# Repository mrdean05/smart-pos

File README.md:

<h2> Battery Powered Two-Layer PCB <h2>

__Note - This is an ongoing project__

## Introduction
This project describes the design and development of a battery-powered, two-layer PCB for a smart point-of-sale (POS) device. The smart point-of-sale device is intended to work with a barcode scanner, identifying items and products with barcode IDs. It comes with a TFT screen and a GUI displaying the product details, including the brand, type, weight, and cost.

## Background of Project
There are numerous small to medium enterprises in Ghana that lack an effective way to track their inventory and finances. The existing implementations are very bulky and expensive, with software that is difficult for an average small shop owner to navigate, and with outrageous monthly subscriptions. This smart point-of-sale (POS) device seeks to simplify and improve the existing solution by creating a quick-to-use, cheap, and portable device. It works with a mobile application that updates the shop owner on every item bought in the shop, giving the shop owner visibility over their shop without their physical presence.

## Hardware and Circuit Design
The PCB was design and developed using KiCad. It comprises of multiple ICs (micocontroller, convertor ICs, and others).

* The Micrcontroller used is the ESP32s3. ESP32s3 is a System-On-Chip(SoC) integrating WiFi and Bluetooth, with peripherals that enable connection with other ICs and modules. 

* The PCBs also integrates ICs such
    - **SY8089 Buck Power Converter** that reduces the input voltage from 5V to 3.3V for the microcontroller and other components in the circuit. It has about 2A output current, with capacitors used as noise filters.
    - **TP4056 and DW01A** that ensure battery health safety by preventing under and over charging.
    - **MAX17048** as a current fuel gauge for the battery.
    - **PCF8523T** serves as an RTC module providing precise time and date information. It is supplied by a coin battery that ensures its continual performance when the device is off.
    - **TCA8418** serves as a keypad scan device through which users can interact with the POS device.
    - **W25N02KVZEIR and W25Q256JVEIQ** that serves as additional flash memory.
    - **PCA95548** serves as additional gpios.

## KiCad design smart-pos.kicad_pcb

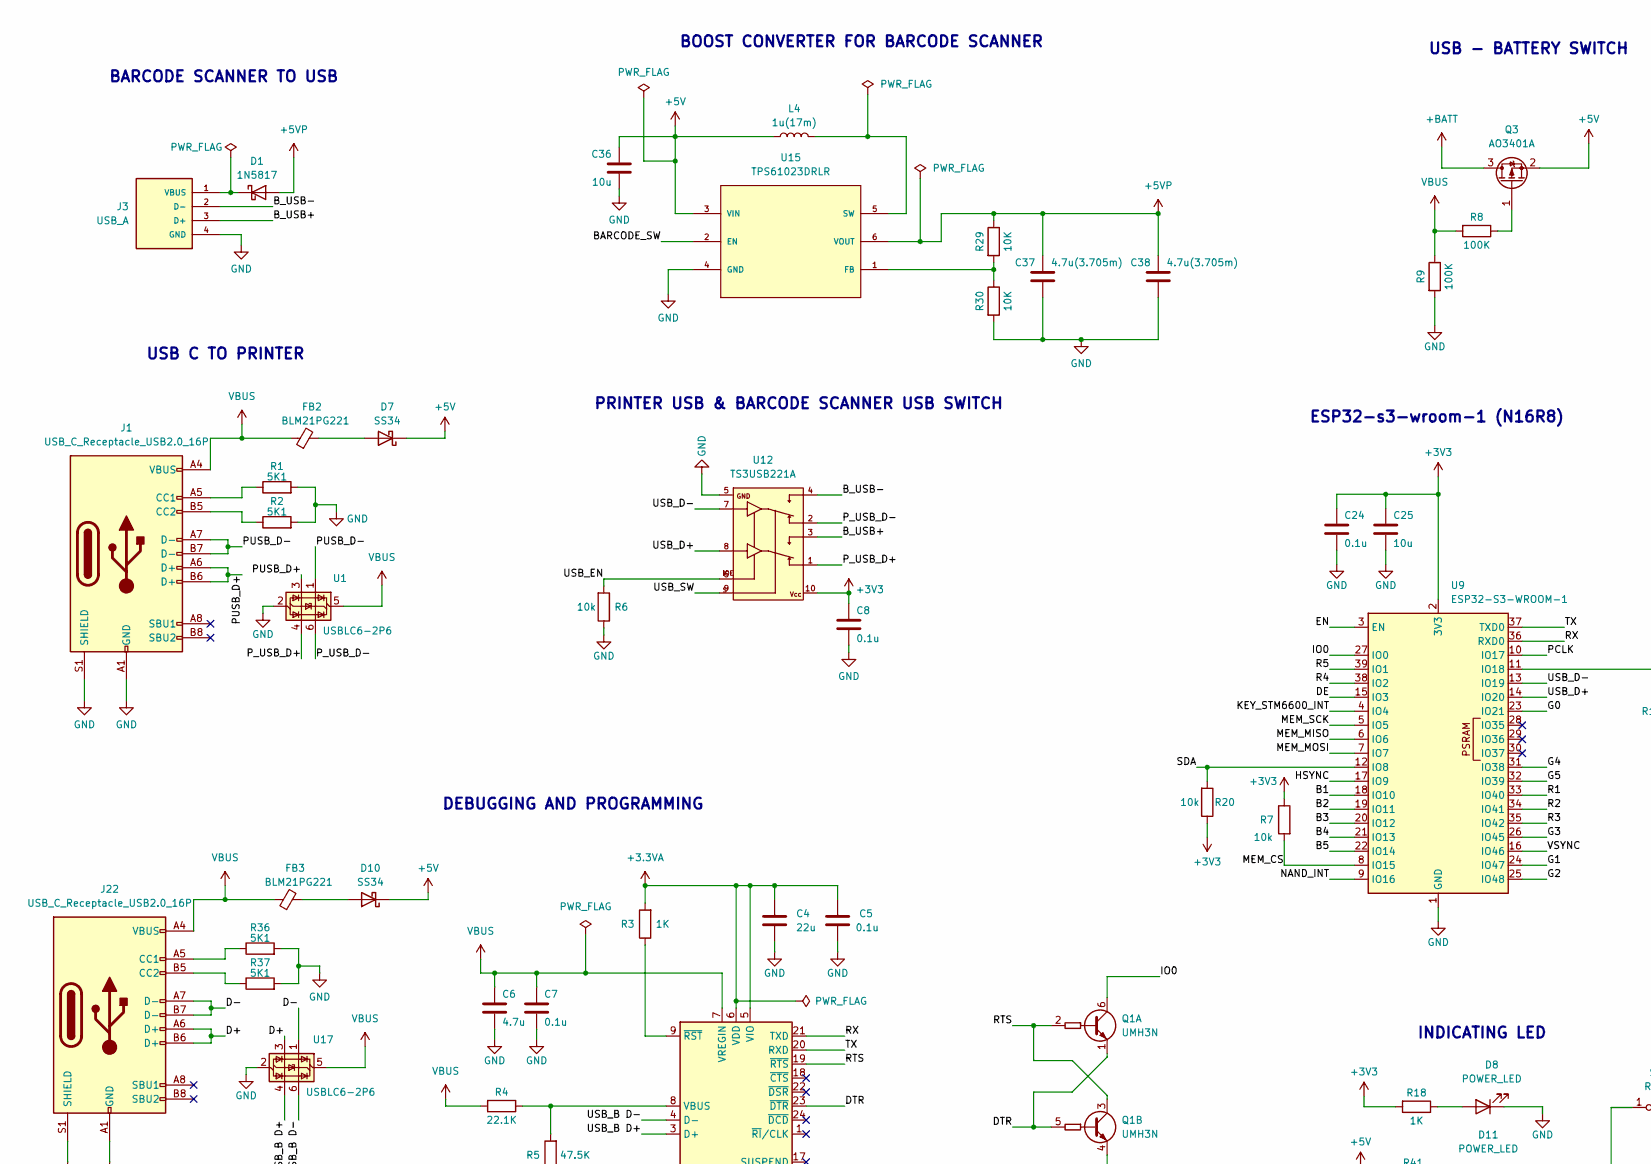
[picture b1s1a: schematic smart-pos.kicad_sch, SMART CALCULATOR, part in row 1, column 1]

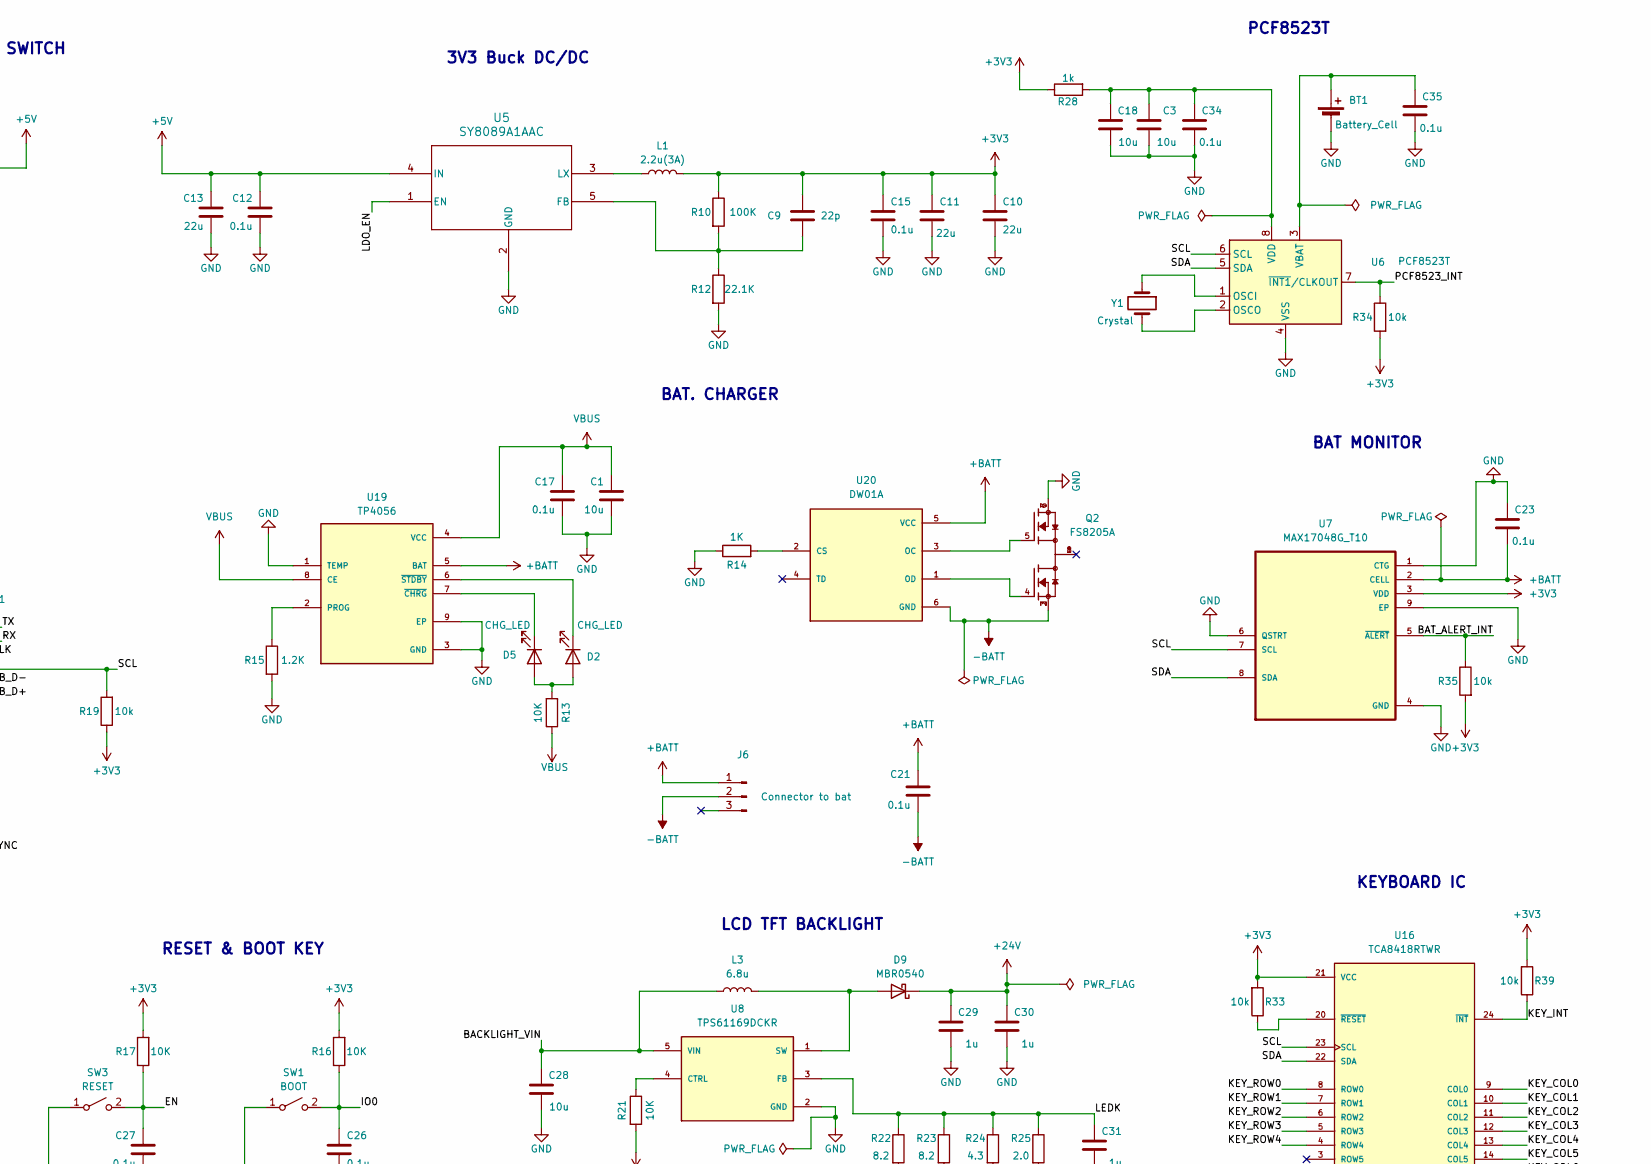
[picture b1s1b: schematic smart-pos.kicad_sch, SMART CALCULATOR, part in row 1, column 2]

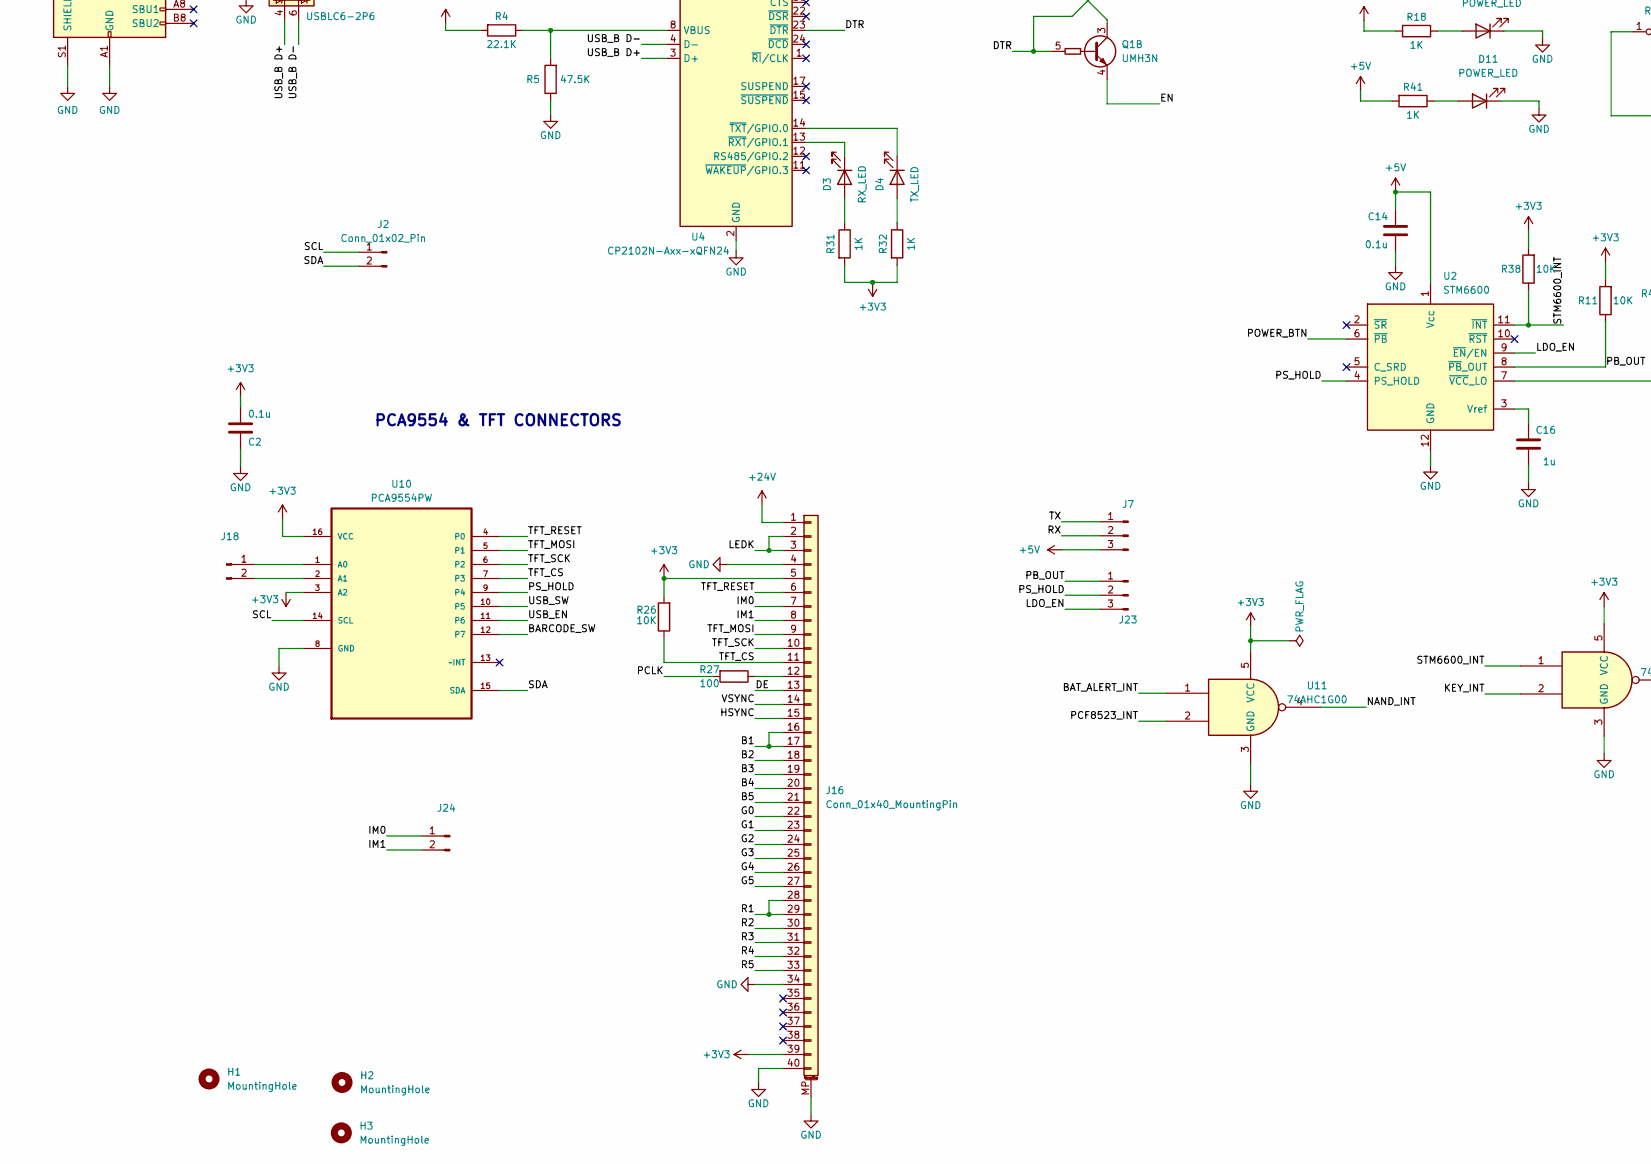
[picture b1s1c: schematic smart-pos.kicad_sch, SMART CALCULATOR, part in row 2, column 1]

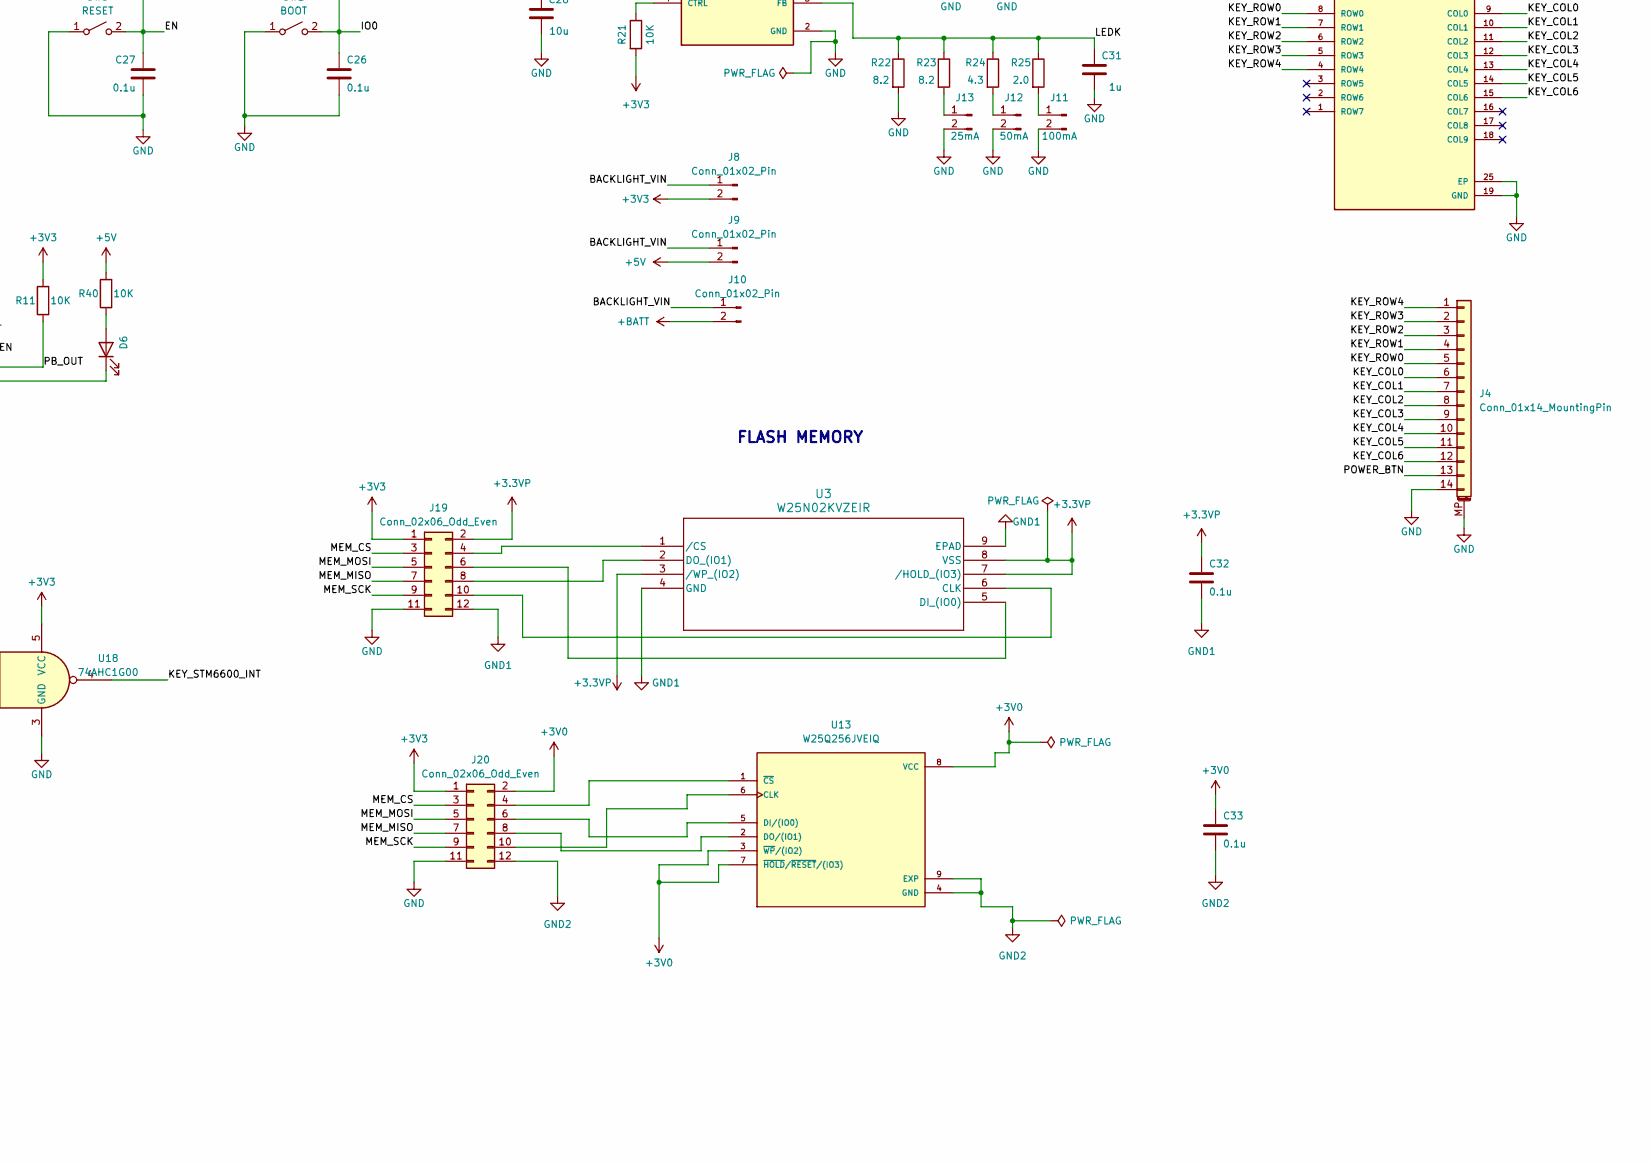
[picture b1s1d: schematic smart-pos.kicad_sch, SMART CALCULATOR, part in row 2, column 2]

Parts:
BT1: Battery_Cell; Battery_Panasonic_CR2032-HFN_Horizontal_CircularHoles
C1, C3, C18, C25, C28, C36: 10u; C_0603_1608Metric_Pad1.08x0.95mm_HandSolder
C2, C5, C7, C8, C12, C14, C15, C17, C21, C23, C24, C26, C27, C32, C33, C34, C35: 0.1u; C_0603_1608Metric_Pad1.08x0.95mm_HandSolder
C4, C10, C11, C13: 22u; C_0603_1608Metric_Pad1.08x0.95mm_HandSolder
C6: 4.7u; C_0603_1608Metric_Pad1.08x0.95mm_HandSolder
C9: 22p; C_0603_1608Metric_Pad1.08x0.95mm_HandSolder
C16, C29, C30, C31: 1u; C_0603_1608Metric_Pad1.08x0.95mm_HandSolder
C37, C38: 4.7u(3.705m); C_0603_1608Metric_Pad1.08x0.95mm_HandSolder
D1: 1N5817; D_SOD-123
D2, D5: CHG_LED; LED_0603_1608Metric_Pad1.05x0.95mm_HandSolder
D3, D6: RX_LED; LED_0603_1608Metric_Pad1.05x0.95mm_HandSolder
D4: TX_LED; LED_0603_1608Metric_Pad1.05x0.95mm_HandSolder
D7, D10: SS34; D_SMA_Handsoldering
D8, D11: POWER_LED; LED_0603_1608Metric_Pad1.05x0.95mm_HandSolder
D9: MBR0540; D_SOD-123
FB2, FB3: BLM21PG221; L_0805_2012Metric_Pad1.05x1.20mm_HandSolder
H1, H2, H3: MountingHole; MountingHole_2.1mm
J1, J22: USB_C_Receptacle_USB2.0_16P; USB_C_Receptacle_GCT_USB4105-xx-A_16P_TopMnt_Horizontal
J2, J8, J9, J10, J18, J24: Conn_01x02_Pin; PinHeader_1x02_P2.54mm_Vertical
J3: USB_A; OST_USB-A1HSW6; PARTREV A
J4: Conn_01x14_MountingPin; Hirose_FH12-14S-0.5SH_1x14-1MP_P0.50mm_Horizontal
J6: Connector to bat; JST_PH_S3B-PH-K_1x03_P2.00mm_Horizontal
J7, J23: Connector to IM0; PinHeader_1x03_P2.54mm_Vertical
J11: 100mA; PinHeader_1x02_P2.54mm_Vertical
J12: 50mA; PinHeader_1x02_P2.54mm_Vertical
J13: 25mA; PinHeader_1x02_P2.54mm_Vertical
J16: Conn_01x40_MountingPin; Hirose_FH12-40S-0.5SH_1x40-1MP_P0.50mm_Horizontal
J19, J20: Conn_02x06_Odd_Even; PinHeader_2x06_P2.54mm_Vertical
L1: 2.2u(3A); L_Cenker_CKCS6045
L3: 6.8u; L_Cenker_CKCS6020
L4: 1u(17m); L_Cenker_CKCS4018
Q1: UMH3N; SOT-363_SC-70-6
Q2: FS8205A; SOT-23-6_Handsoldering; PARTREV 1.7
Q3: AO3401A; SOT-23
R1, R2, R36, R37: 5K1; R_0603_1608Metric_Pad0.98x0.95mm_HandSolder
R3, R14, R18, R31, R32, R41: 1K; R_0603_1608Metric_Pad0.98x0.95mm_HandSolder
R4, R12: 22.1K; R_0603_1608Metric_Pad0.98x0.95mm_HandSolder
R5: 47.5K; R_0603_1608Metric_Pad0.98x0.95mm_HandSolder
R6, R7, R19, R20, R33, R34, R35, R39: 10k; R_0603_1608Metric_Pad0.98x0.95mm_HandSolder
R8, R9, R10: 100K; R_0603_1608Metric_Pad0.98x0.95mm_HandSolder
R11, R13, R16, R17, R21, R26, R29, R30, R38, R40: 10K; R_0603_1608Metric_Pad0.98x0.95mm_HandSolder
R15: 1.2K; R_0603_1608Metric_Pad0.98x0.95mm_HandSolder
R22, R23: 8.2; R_0603_1608Metric_Pad0.98x0.95mm_HandSolder
R24: 4.3; R_0603_1608Metric_Pad0.98x0.95mm_HandSolder
R25: 2.0; R_0603_1608Metric_Pad0.98x0.95mm_HandSolder
R27: 100; R_0603_1608Metric_Pad0.98x0.95mm_HandSolder
R28: 1k; R_0603_1608Metric_Pad0.98x0.95mm_HandSolder
SW1: BOOT; SW_SPST_PTS810
SW3: RESET; SW_SPST_PTS810
U1, U17: USBLC6-2P6; SOT-666
U2: STM6600; TDFN-12_2x3mm_P0.5mm
U3: W25N02KVZEIR; W25N02-M
U4: CP2102N-Axx-xQFN24; QFN-24-1EP_4x4mm_P0.5mm_EP2.6x2.6mm
U5: SY8089A1AAC; SY8089AAAC_SGY
U6: PCF8523T; SOIC-8_3.9x4.9mm_P1.27mm
U7: MAX17048G_T10; SON50P200X200X80-9N
U8: TPS61169DCKR; SOT65P210X110-5N; PARTREV A
U9: ESP32-S3-WROOM-1
U10: PCA9554PW; SOP65P640X120-16N; MPN PCA9554PW
U11, U18: 74AHC1G00; SOT-23-5_HandSoldering
U12: TS3USB221A; QFN-10-RSE
U13: W25Q256JVEIQ; SON127P600X800X80-9N; PARTREV G
U15: TPS61023DRLR; DRL0006A; PARTNUMBER TPS61023DRL
U16: TCA8418RTWR; QFN50P400X400X80-25N; PARTREV G
U19: TP4056; SOP127P600X175-9N
U20: DW01A; SOT-23-6_Handsoldering; PARTREV 1.8
Y1: Crystal; Crystal_C26-LF_D2.1mm_L6.5mm_Horizontal

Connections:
+3.3VA: C4.1, C5.1, R3.2, U4.5 (VIO), U4.6 (VDD)
+3.3VP: C32.1, J19.2, U3.3 (/WP_(IO2)), U3.7 (/HOLD_(IO3)), U3.8 (VSS)
+3V0: C33.1, J20.2, U13.3 (~WP/(IO2)), U13.7 (~HOLD/~RESET/(IO3)), U13.8 (VCC)
+3V3: C2.2, C8.1, C9.1, C10.1, C11.1, C15.1, C24.1, C25.1, J8.2, J16.5, J16.39, J19.1, J20.1, L1.2, R7.1, R10.1, R11.2, R16.2, R17.2, R18.2, R19.1, R20.1, R21.2, R26.2, R28.1, R31.2, R32.2, R33.2, R34.2, R35.2, R38.2, R39.2, U7.3 (VDD), U9.2 (3V3), U10.3 (A2), U10.16 (VCC), U11.5 (VCC), U12.10, U16.21 (VCC), U18.5 (VCC)
+5V: C12.1, C13.1, C14.1, C36.1, D7.1 (K), D10.1 (K), J7.3, J9.2, L4.1, Q3.2 (S), R40.2, R41.2, U2.1 (Vcc), U5.4 (IN), U15.3 (VIN); also elsewhere on the board
+5VP: C37.1, C38.1, D1.2 (A), R29.1, U15.6 (VOUT)
+24V: C29.1, C30.1, D9.1 (K), J16.1
+BATT: C21.1, C23.2, J6.1, J10.2, Q3.3 (D), U7.2 (CELL), U19.5 (BAT), U20.5 (VCC)
-BATT: C21.2, J6.2, Q2.2, Q2.3, U20.6 (GND)
/B1: J16.16, J16.17, U9.18 (IO10)
/B2: J16.18, U9.19 (IO11)
/B3: J16.19, U9.20 (IO12)
/B4: J16.20, U9.21 (IO13)
/B5: J16.21, U9.22 (IO14)
/BACKLIGHT_VIN: C28.1, J8.1, J9.1, J10.1, L3.1, U8.5 (VIN)
/BARCODE_SW: U10.12 (P7), U15.2 (EN)
/BAT_ALERT_INT: R35.1, U7.5 (~ALERT), U11.1
/B_USB+: J3.3 (D+), U12.3
/B_USB-: J3.2 (D-), U12.4
/D+: J22.A6 (D+), J22.B6 (D+), U17.3 (I/O2)
/D-: J22.A7 (D-), J22.B7 (D-), U17.1 (I/O1)
/DE: J16.13, U9.15 (IO3)
/DTR: Q1.1 (E1), Q1.5 (B2), U4.23 (~DTR)
/EN: C27.1, Q1.4 (E2), R17.1, SW3.2 (B), U9.3 (EN)
/G0: J16.22, U9.23 (IO21)
/G1: J16.23, U9.24 (IO47)
/G2: J16.24, U9.25 (IO48)
/G3: J16.25, U9.26 (IO45)
/G4: J16.26, U9.31 (IO38)
/G5: J16.27, U9.32 (IO39)
/HSYNC: J16.15, U9.17 (IO9)
/IM0: J16.7, J24.1
/IM1: J16.8, J24.2
/IO0: C26.1, Q1.6 (C1), R16.1, SW1.2 (B), U9.27 (IO0)
/KEY_COL0: J4.6, U16.9 (COL0)
/KEY_COL1: J4.7, U16.10 (COL1)
/KEY_COL2: J4.8, U16.11 (COL2)
/KEY_COL3: J4.9, U16.12 (COL3)
/KEY_COL4: J4.10, U16.13 (COL4)
/KEY_COL5: J4.11, U16.14 (COL5)
/KEY_COL6: J4.12, U16.15 (COL6)
/KEY_INT: R39.1, U16.24 (~INT), U18.2
/KEY_ROW0: J4.5, U16.8 (ROW0)
/KEY_ROW1: J4.4, U16.7 (ROW1)
/KEY_ROW2: J4.3, U16.6 (ROW2)
/KEY_ROW3: J4.2, U16.5 (ROW3)
/KEY_ROW4: J4.1, U16.4 (ROW4)
/KEY_STM6600_INT: U9.4 (IO4), U18.4
/LDO_EN: J23.3, U2.9 (~EN/EN), U5.1 (EN)
/LEDK: C31.1, J16.2, J16.3, R22.1, R23.1, R24.1, R25.1, U8.3 (FB)
/MEM_CS: J19.3, J20.3, R7.2, U9.8 (IO15)
/MEM_MISO: J19.7, J20.7, U9.6 (IO6)
/MEM_MOSI: J19.5, J20.5, U9.7 (IO7)
/MEM_SCK: J19.9, J20.9, U9.5 (IO5)
/NAND_INT: U9.9 (IO16), U11.4
/PB_OUT: J23.1, R11.1, U2.8 (~PB_OUT)
/PCF8523_INT: R34.1, U6.7 (~INT1/CLKOUT), U11.2
/PCLK: R27.2, U9.10 (IO17)
/POWER_BTN: J4.13, U2.6 (~PB)
/PS_HOLD: J23.2, U2.4 (PS_HOLD), U10.9 (P4)
/PUSB_D+: J1.A6 (D+), J1.B6 (D+), U1.3 (I/O2)
/PUSB_D-: J1.A7 (D-), J1.B7 (D-), U1.1 (I/O1)
/P_USB_D+: U1.4 (I/O2), U12.1
/P_USB_D-: U1.6 (I/O1), U12.2
/R1: J16.28, J16.29, U9.33 (IO40)
/R2: J16.30, U9.34 (IO41)
/R3: J16.31, U9.35 (IO42)
/R4: J16.32, U9.38 (IO2)
/R5: J16.33, U9.39 (IO1)
/RTS: Q1.2 (B1), Q1.3 (C2), U4.19 (~RTS)
/RX: J7.2, U4.21 (TXD), U9.36 (RXD0)
/SCL: J2.1, R19.2, U6.6 (SCL), U7.7 (SCL), U9.11 (IO18), U10.14 (SCL), U16.23 (SCL)
/SDA: J2.2, R20.2, U6.5 (SDA), U7.8 (SDA), U9.12 (IO8), U10.15 (SDA), U16.22 (SDA)
/STM6600_INT: R38.1, U2.11 (~INT), U18.1
/TFT_CS: J16.11, R26.1, U10.7 (P3)
/TFT_MOSI: J16.9, U10.5 (P1)
/TFT_RESET: J16.6, U10.4 (P0)
/TFT_SCK: J16.10, U10.6 (P2)
/TX: J7.1, U4.20 (RXD), U9.37 (TXD0)
/USB_B D+: U4.3 (D+), U17.4 (I/O2)
/USB_B D-: U4.4 (D-), U17.6 (I/O1)
/USB_D+: U9.14 (IO20), U12.8
/USB_D-: U9.13 (IO19), U12.7
/USB_EN: R6.2, U10.11 (P6), U12.6
/USB_SW: U10.10 (P5), U12.9
/VSYNC: J16.14, U9.16 (IO46)
GND: BT1.2 (-), C1.2, C2.1, C3.2, C4.2, C5.2, C6.2, C7.2, C8.2, C10.2, C11.2, C12.2, C13.2, C14.2, C15.2, C16.2, C17.2, C18.2, C23.1, C24.2, C25.2, C26.2, C27.2, C28.2, C29.2, C30.2, C31.2, C34.2, C35.2, C36.2, C37.2, C38.2, D8.1 (K), D11.1 (K), J1.A1 (GND), J1.A12 (GND), J1.B1 (GND), J1.B12 (GND), J1.S1 (SHIELD), J3.4 (GND), J4.14, J4.MP (MountPin), J11.2, J12.2, J13.2, J16.4, J16.34, J16.40, J16.MP (MountPin), J19.11, J20.11, J22.A1 (GND), J22.A12 (GND), J22.B1 (GND), J22.B12 (GND), J22.S1 (SHIELD), Q2.6, Q2.7, R1.2, R2.2, R5.1, R6.1, R9.2, R12.2, R14.1, R15.2, R22.2, R30.2, R36.2, R37.2, SW1.1 (A), SW3.1 (A), U1.2 (GND), U2.12 (GND), U4.2 (GND), U4.25 (GND), U5.2 (GND), U6.4 (VSS), U7.1 (CTG), U7.4 (GND), U7.6 (QSTRT), U7.9 (EP), U8.2 (GND), U9.1 (GND), U9.40 (GND), U9.41 (GND), U10.8 (GND), U11.3 (GND), U12.5, U15.4 (GND), U16.19 (GND), U16.25 (EP), U17.2 (GND), U18.3 (GND), U19.1 (TEMP), U19.3 (GND), U19.9 (EP)
GND1: C32.2, J19.12, U3.4 (GND), U3.9 (EPAD)
GND2: C33.2, J20.12, U13.4 (GND), U13.9 (EXP)
unnamed: BT1.1 (+), C35.1, U6.3 (VBAT)
unnamed: D1.1 (K), J3.1 (VBUS)
unnamed: D2.2 (A), D5.2 (A), R13.2
unnamed: D2.1 (K), U19.6 (~STDBY)
unnamed: D3.2 (A), R31.1
unnamed: D3.1 (K), U4.13 (~RXT/GPIO.1)
unnamed: D4.2 (A), R32.1
unnamed: D4.1 (K), U4.14 (~TXT/GPIO.0)
unnamed: D5.1 (K), U19.7 (~CHRG)
unnamed: D6.2 (A), R40.1
unnamed: D6.1 (K), U2.7 (~VCC_LO)
unnamed: D7.2 (A), FB2.2
unnamed: D8.2 (A), R18.1
unnamed: D9.2 (A), L3.2, U8.1 (SW)
unnamed: D10.2 (A), FB3.2
unnamed: D11.2 (A), R41.1
unnamed: J1.A5 (CC1), R1.1
unnamed: J1.B5 (CC2), R2.1
unnamed: J11.1, R25.2
unnamed: J12.1, R24.2
unnamed: J13.1, R23.2
unnamed: J16.12, R27.1
unnamed: J18.1, U10.1 (A0)
unnamed: J18.2, U10.2 (A1)
unnamed: J19.4, U3.1 (/CS)
unnamed: J19.6, U3.5 (DI_(IO0))
unnamed: J19.8, U3.2 (DO_(IO1))
unnamed: J19.10, U3.6 (CLK)
unnamed: J20.4, U13.1 (~CS)
unnamed: J20.6, U13.5 (DI/(IO0))
unnamed: J20.8, U13.2 (DO/(IO1))
unnamed: J20.10, U13.6 (CLK)
unnamed: J22.A5 (CC1), R36.1
unnamed: J22.B5 (CC2), R37.1
unnamed: Q3.1 (G), R8.1
unnamed: C16.1, U2.3 (Vref)
unnamed: R4.1, R5.2, U4.8 (VBUS)
unnamed: R3.1, U4.9 (~RST)
unnamed: C9.2, R10.2, R12.1, U5.5 (FB)
unnamed: L1.1, U5.3 (LX)
unnamed: U6.1 (OSCI), Y1.1
unnamed: U6.2 (OSCO), Y1.2
unnamed: C3.1, C18.1, C34.1, R28.2, U6.8 (VDD)
unnamed: R21.1, U8.4 (CTRL)
unnamed: R29.2, R30.1, U15.1 (FB)
unnamed 134: L4.2, U15.5 (SW); also elsewhere on the board
unnamed: R33.1, U16.20 (~RESET)
unnamed: R15.1, U19.2 (PROG)
unnamed: R14.2, U20.2 (CS)
unnamed: Q2.5, U20.3 (OC)
unnamed: Q2.4, U20.1 (OD)
VBUS: C1.1, C6.1, C7.1, C17.1, FB2.1, FB3.1, J1.A4 (VBUS), J1.A9 (VBUS), J1.B4 (VBUS), J1.B9 (VBUS), J22.A4 (VBUS), J22.A9 (VBUS), J22.B4 (VBUS), J22.B9 (VBUS), R4.2, R8.2, R9.1, R13.1, U1.5 (VBUS), U4.7 (VREGIN), U17.5 (VBUS), U19.4 (VCC), U19.8 (CE)

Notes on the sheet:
FLASH MEMORY
DEBUGGING AND PROGRAMMING
PCA9554 & TFT CONNECTORS
3V3 Buck DC/DC
LCD TFT BACKLIGHT
USB - BATTERY SWITCH
USB C TO PRINTER
RESET & BOOT KEY
ESP32-s3-wroom-1 (N16R8)
BOOST CONVERTER FOR BARCODE SCANNER
INDICATING LED
PRINTER USB & BARCODE SCANNER USB SWITCH
PCF8523T
KEYBOARD IC
BAT. CHARGER
BAT MONITOR
BARCODE SCANNER TO USB

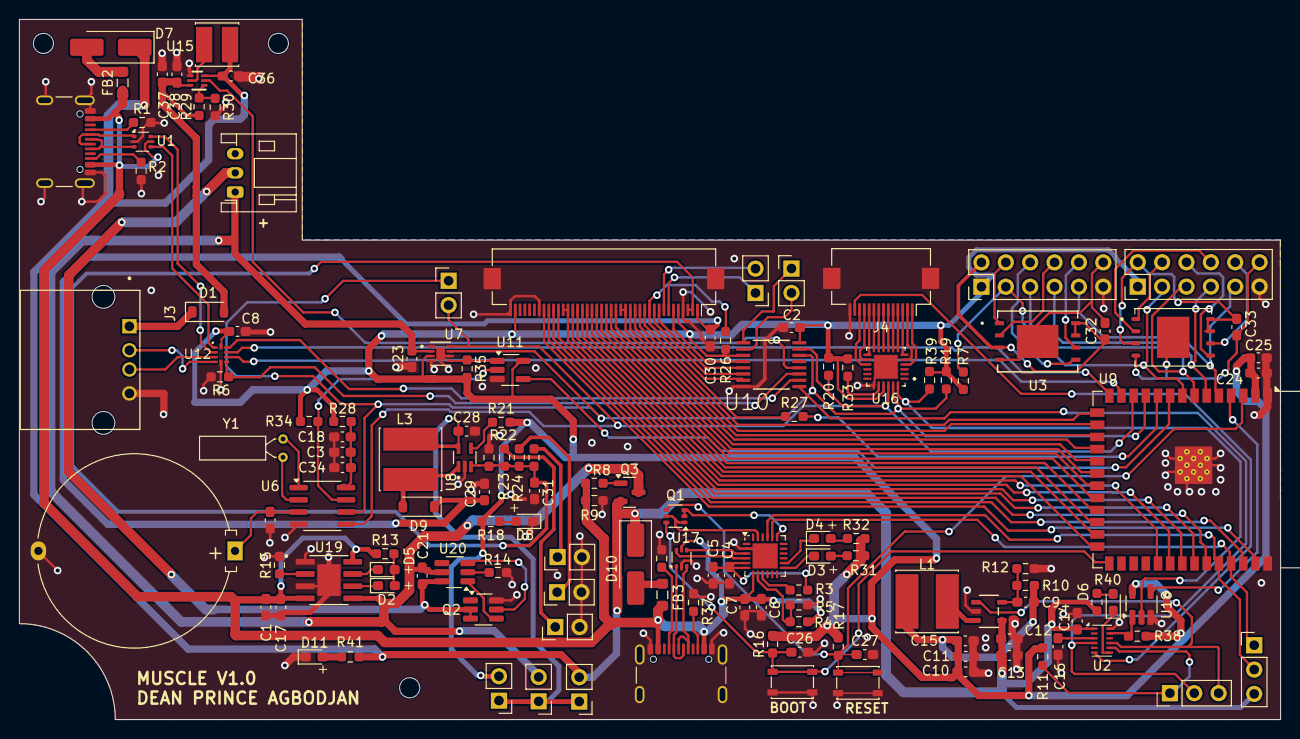
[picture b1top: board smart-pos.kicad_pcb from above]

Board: 2 copper layers, 131.5 x 73.0 mm, 140 parts (0 on the bottom side), 141 nets.

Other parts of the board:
locked: 1u(17m); L_Cenker_CKCS4018

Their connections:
+5V: locked.1; also elsewhere on the board
unnamed 134: locked.2; also elsewhere on the board

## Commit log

2024-12-04 pos version 1.00
2024-12-04 added images
2024-12-06 Edited Readme.md file
